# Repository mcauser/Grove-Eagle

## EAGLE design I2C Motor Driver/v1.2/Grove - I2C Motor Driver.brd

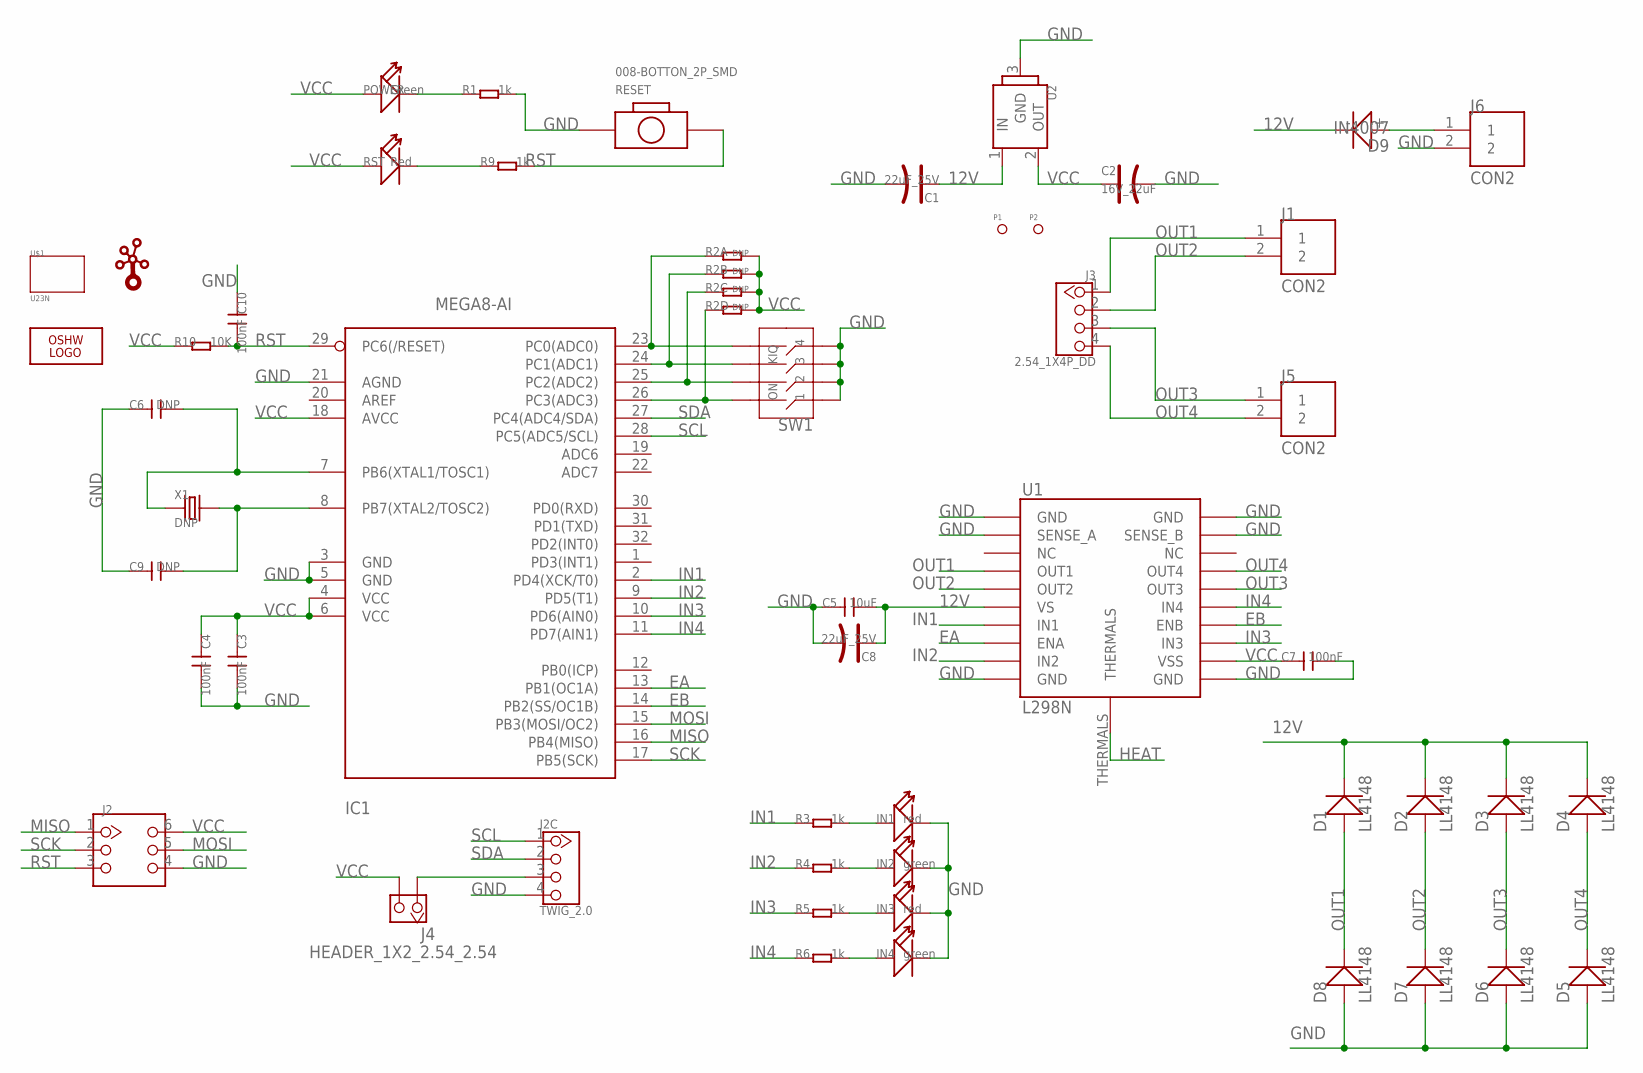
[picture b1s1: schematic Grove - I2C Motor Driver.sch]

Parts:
C1, C8: 22uF_25V; AVX-C
C2: 16V_22uF; AVX-B
C3, C4, C7: 100nF; 0603
C5: 10uF; 0805
C6, C9: DNP; 0603_S
C10: 100nF; 0603_S
D1, D2, D3, D4, D5, D6, D7, D8: LL4148; SOD123
D9: IN4007; D2010@1
I2C: TWIG_2.0; 2.0_1X4
IC1: MEGA8-AI; TQFP32-08
IN1, IN3: red; D0603
IN2, IN4: green; D0603
J1, J5, J6: CON2
J2: HEADER-2X3P-60/35MIL; 2X3P-2.54-65/35MIL
J3: 2.54_1X4P_DD; CK_1X4
J4: HEADER_1X2_2.54_2.54; 65*35
LOGO2: LOGO-OSHW-FILLX0200-NT; OSHW_FILLX200_NOTEXT
P1, P2: PAD-MARK; ROUND-MARK-1.0
POWER: Green; D0603
R1, R3, R4, R5, R6, R9: 1k; 0603-1
R2: DNP; 1206-8-3.3X2.4
R10: 10K; 0603-1
RESET: 008-BOTTON_2P_SMD; BOTTON_1
RST: Red; D0603
SW1: SWITCH-KM-04'KM-04'; 8P-SMD-11.8X6.8X3.3H
U1: L298N; POWERSO20
U2: 78M05-TO252; TO252
U$1: U23N; U2*3N
U$3: TWIGLOGOTWIGLOGO_SMALL; TWIGLOGO_SMALL
X1: DNP; 2P-SMD-5X3.2

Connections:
12V: C1.+, C5.2, C8.+, D1.-, D2.-, D3.-, D4.-, D9.-, U1.P$6 (VS), U2.1 (IN)
EA: IC1.13 (PB1(OC1A)), U1.P$8 (ENA)
EB: IC1.14 (PB2(SS/OC1B)), U1.P$14 (ENB)
GND: C1.-, C2.-, C3.2, C4.2, C5.1, C6.1, C7.2, C8.-, C9.1, C10.1, D5.+, D6.+, D7.+, D8.+, I2C.4, IC1.3 (GND), IC1.5 (GND), IC1.21 (AGND), IN1.-, IN2.-, IN3.-, IN4.-, J2.4, J6.2, R1.2, RESET.1, SW1.1, SW1.2, SW1.3, SW1.4, U1.P$1 (GND), U1.P$2 (SENSE_A), U1.P$10 (GND), U1.P$11 (GND), U1.P$19 (SENSE_B), U1.P$20 (GND), U2.3 (GND)
HEAT: U1.THERMALS
IN1: IC1.2 (PD4(XCK/T0)), R3.1, U1.P$7 (IN1)
IN2: IC1.9 (PD5(T1)), R4.1, U1.P$9 (IN2)
IN3: IC1.10 (PD6(AIN0)), R5.1, U1.P$13 (IN3)
IN4: IC1.11 (PD7(AIN1)), R6.1, U1.P$15 (IN4)
MISO: IC1.16 (PB4(MISO)), J2.1
MOSI: IC1.15 (PB3(MOSI/OC2)), J2.5
unnamed: IN3.+, R5.2
unnamed: I2C.3, J4.1
unnamed: POWER.-, R1.1
unnamed: IC1.23 (PC0(ADC0)), R2.1, SW1.5
unnamed: IC1.24 (PC1(ADC1)), R2.2 (1), SW1.6
unnamed: IC1.25 (PC2(ADC2)), R2.3 (1), SW1.7
unnamed: C6.2, IC1.7 (PB6(XTAL1/TOSC1)), X1.1
unnamed: C9.2, IC1.8 (PB7(XTAL2/TOSC2)), X1.2
unnamed: R9.1, RST.-
unnamed: IC1.26 (PC3(ADC3)), R2.4 (1), SW1.8
unnamed: D9.+, J6.1
unnamed: IN1.+, R3.2
unnamed: IN2.+, R4.2
unnamed: IN4.+, R6.2
OUT1: D1.+, D8.-, J1.1, J3.1, U1.P$4 (OUT1)
OUT2: D2.+, D7.-, J1.2, J3.2, U1.P$5 (OUT2)
OUT3: D3.+, D6.-, J3.3, J5.1, U1.P$16 (OUT3)
OUT4: D4.+, D5.-, J3.4, J5.2, U1.P$17 (OUT4)
RST: C10.2, IC1.29 (PC6(/RESET)), J2.3, R9.2, R10.2, RESET.P$2 (2)
SCK: IC1.17 (PB5(SCK)), J2.2
SCL: I2C.1, IC1.28 (PC5(ADC5/SCL))
SDA: I2C.2, IC1.27 (PC4(ADC4/SDA))
VCC: C2.+, C3.1, C4.1, C7.1, IC1.4 (VCC), IC1.6 (VCC), IC1.18 (AVCC), J2.6, J4.2, POWER.+, R2.5 (2), R2.6 (2), R2.7 (2), R2.8 (2), R10.1, RST.+, U1.P$12 (VSS), U2.2 (OUT)

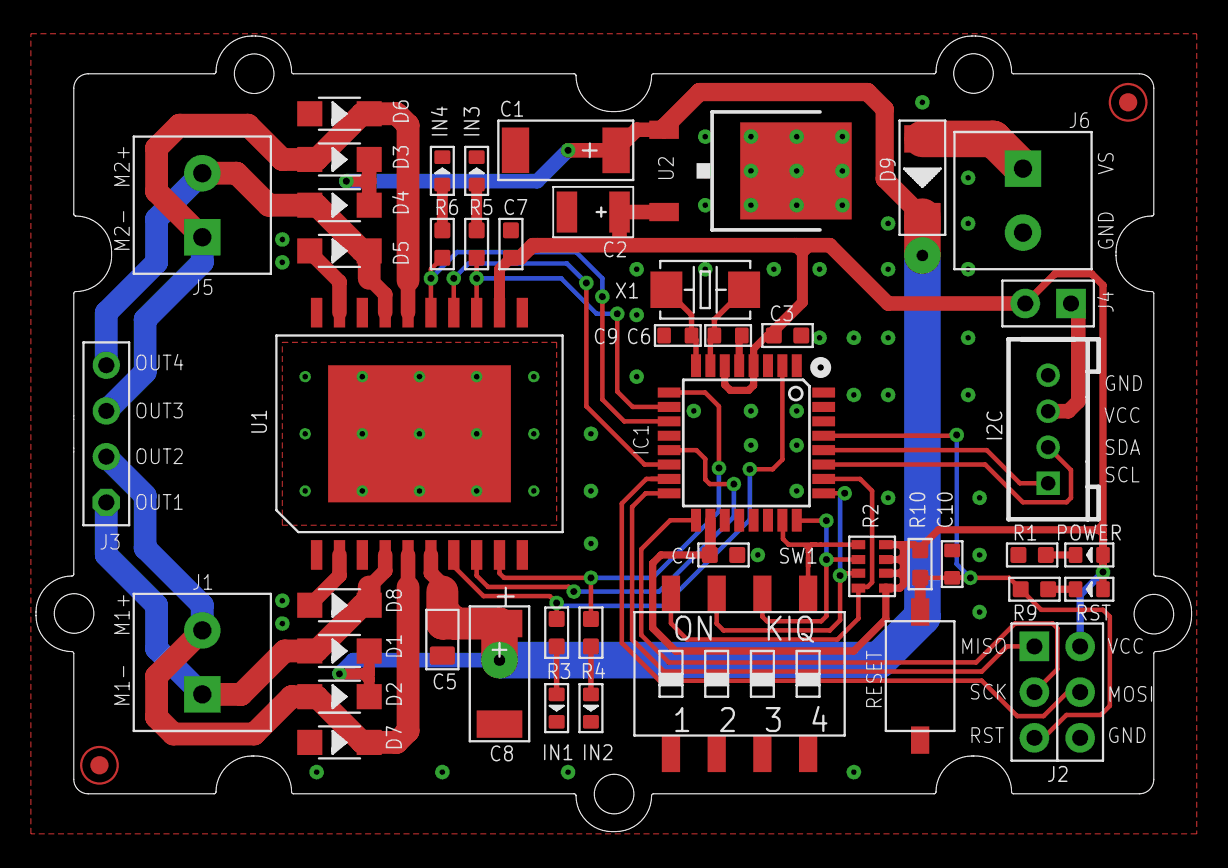
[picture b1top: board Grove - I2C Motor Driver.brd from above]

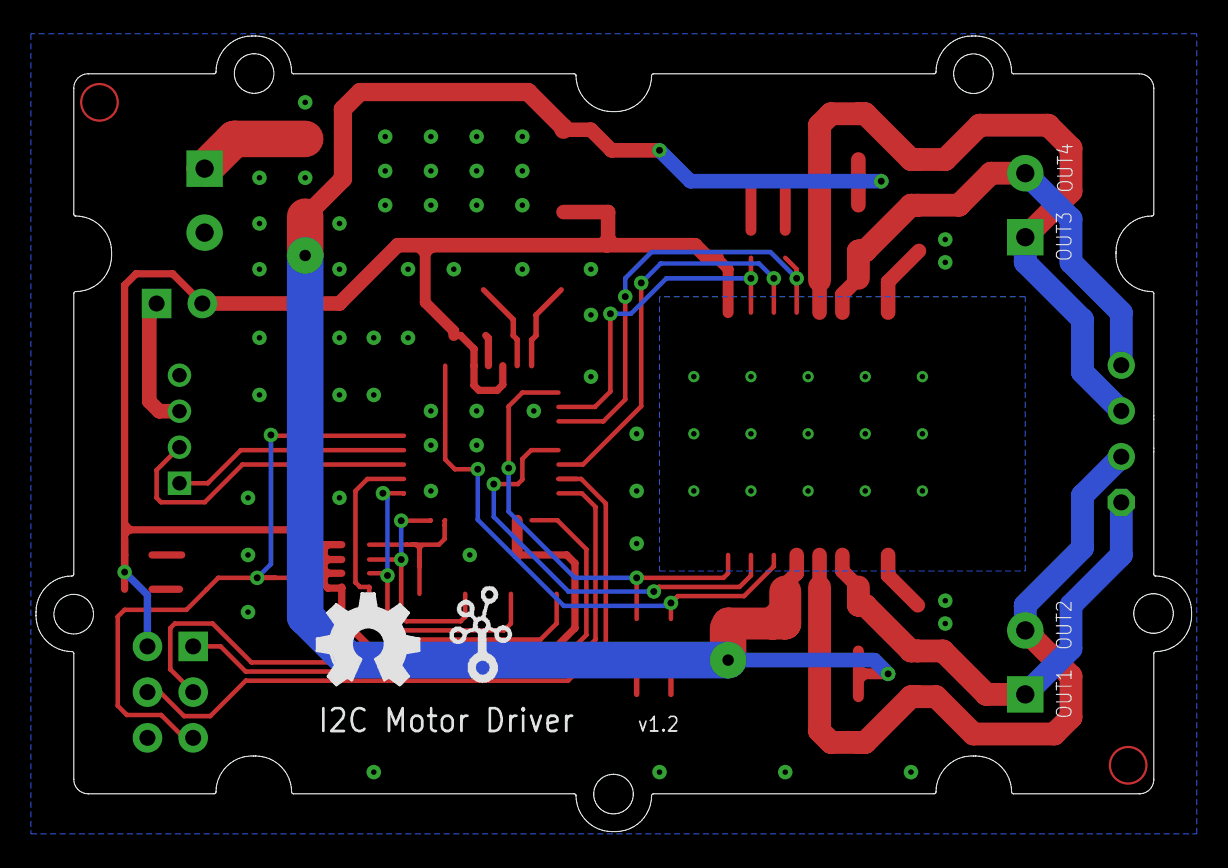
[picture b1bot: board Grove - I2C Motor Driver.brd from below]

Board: 2 copper layers, 64.2 x 44.2 mm, 51 parts (2 on the bottom side), 33 nets.

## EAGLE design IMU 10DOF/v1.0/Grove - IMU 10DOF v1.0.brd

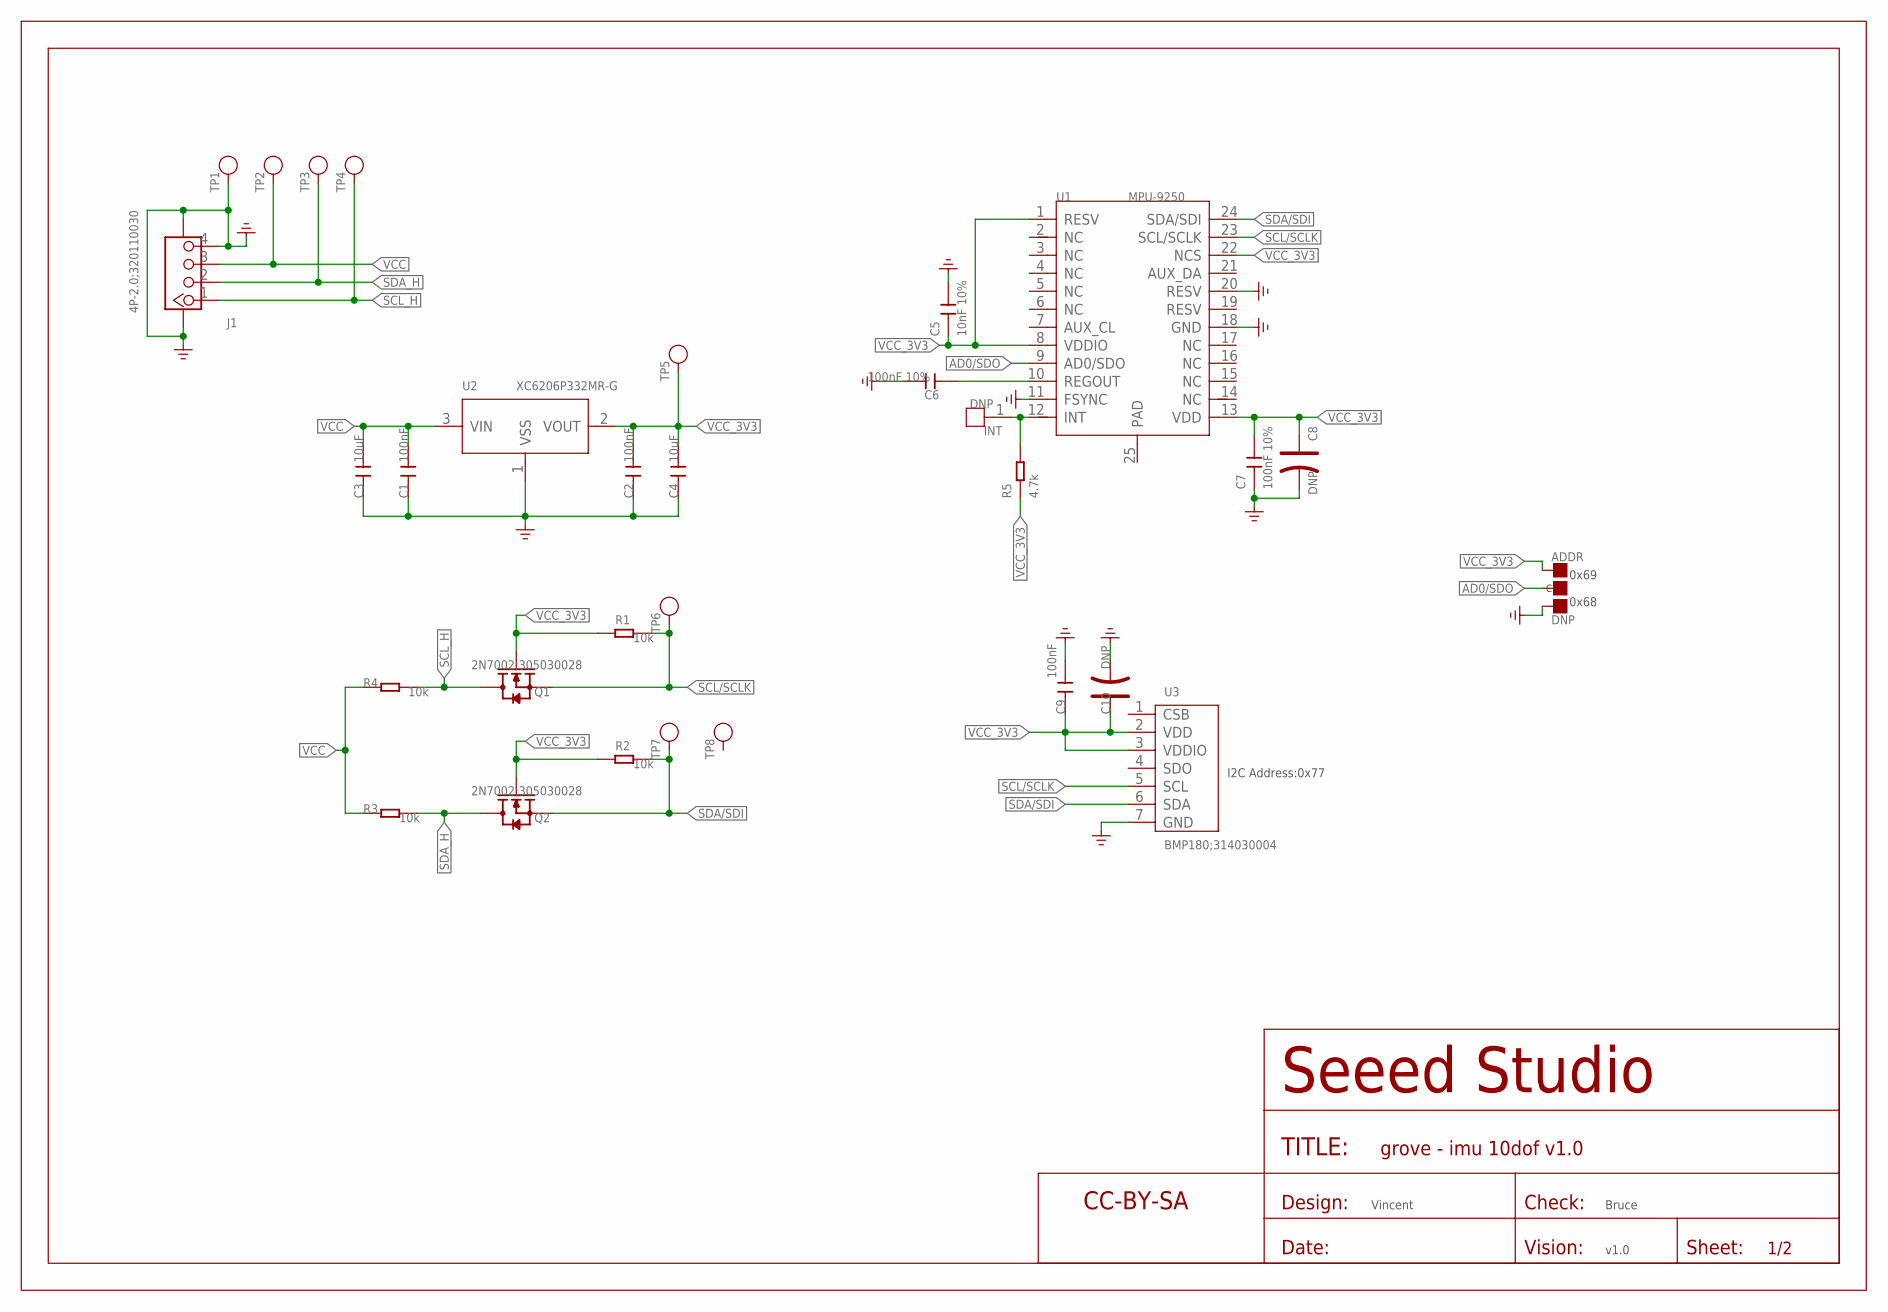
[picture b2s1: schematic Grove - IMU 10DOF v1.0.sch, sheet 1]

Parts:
ADDR: DNP; 3P-SMD-L4.1*W1.5MM
C1, C2, C9: 100nF; C0603
C3, C4: 10uF; C0805
C5: 10nF 10%; C0603
C6, C7: 100nF 10%; C0603
C8, C10: DNP; AVX-A
INT: DNP; 1P-65/35MIL
J1: 4P-2.0;320110030; 4P-SMD-2.0
Q1, Q2: 2N7002;305030028; SOT-23
R1, R2, R3, R4: 10k; R0603
R5: 4.7k; R0603
TP1, TP2, TP3, TP4, TP5, TP6, TP7, TP8: DNP; TP-D45MIL
U1: MPU-9250; LEAD-QFN24
U2: XC6206P332MR-G; SOT-23
U3: BMP180;314030004; LGA-7
U$1: SEEEDSTUDIO-OPEN-SCH-FRAME; SEEEDSTUDIO-PCB-FRAME

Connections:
AD0/SDO: ADDR.MM (C), U1.9 (AD0/SDO)
GND: ADDR.11 (R), C1.1, C2.1, C3.1, C4.1, C5.2, C6.2, C7.1, C8.-, C9.2, C10.-, J1.4, J1.SS1, J1.SS2, TP1.T, U1.11 (FSYNC), U1.18 (GND), U1.20 (RESV), U2.1 (VSS), U3.7 (GND)
unnamed: C6.1, U1.10 (REGOUT)
unnamed: INT.1, R5.2, U1.12 (INT)
SCL/SCLK: Q1.2 (S), R1.2, TP6.T, U1.23 (SCL/SCLK), U3.5 (SCL)
SCL_H: J1.1, Q1.3 (D), R4.2, TP4.T
SDA/SDI: Q2.2 (S), R2.2, TP7.T, U1.24 (SDA/SDI), U3.6 (SDA)
SDA_H: J1.2, Q2.3 (D), R3.2, TP3.T
VCC: C1.2, C3.2, J1.3, R3.1, R4.1, TP2.T, U2.3 (VIN)
VCC_3V3: ADDR.00 (L), C2.2, C4.2, C5.1, C7.2, C8.+, C9.1, C10.+, Q1.1 (G), Q2.1 (G), R1.1, R2.1, R5.1, TP5.T, U1.1 (RESV), U1.8 (VDDIO), U1.13 (VDD), U1.22 (NCS), U2.2 (VOUT), U3.2 (VDD), U3.3 (VDDIO)

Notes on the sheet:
Vincent
Bruce
v1.0
0x69
0x68
I2C Address:0x77

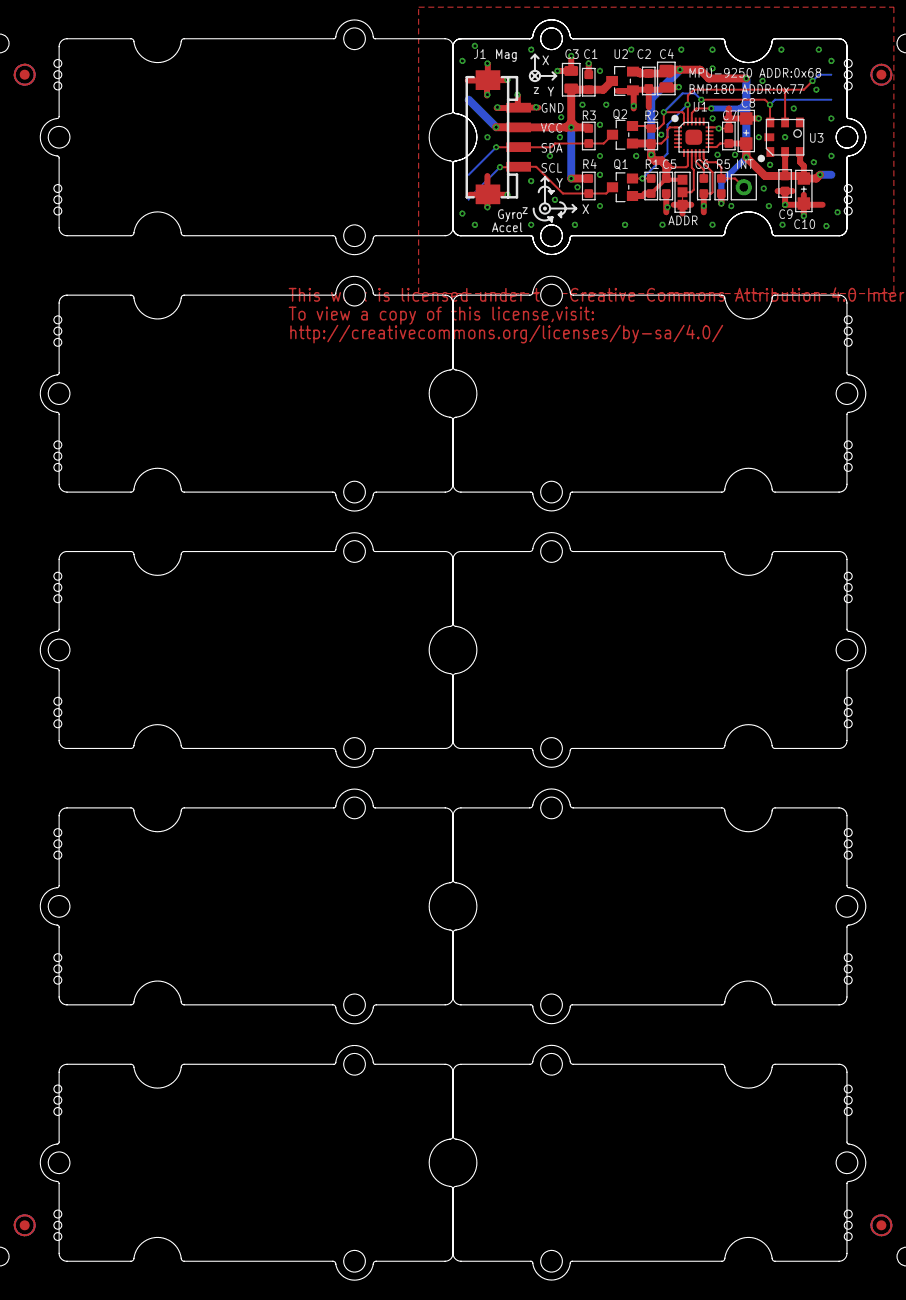
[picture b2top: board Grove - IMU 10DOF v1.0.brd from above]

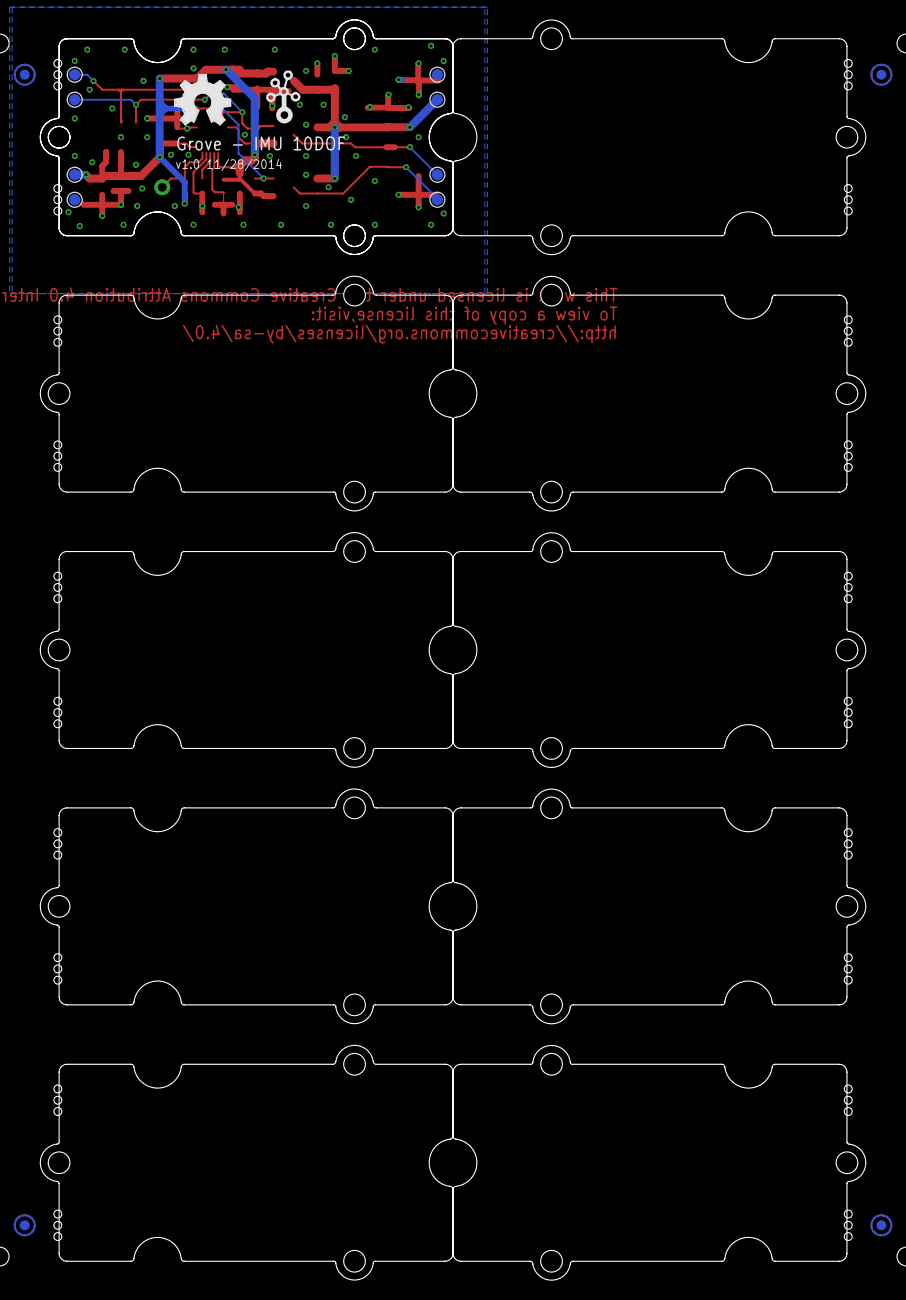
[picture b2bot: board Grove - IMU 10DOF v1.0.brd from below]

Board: 2 copper layers, 83.8 x 128.0 mm, 53 parts (14 on the bottom side), 10 nets.

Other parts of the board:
P1, P2, P3, P4, P5, P6, P7, P8: ROUND-MARK-1.0
U4, U5, U6, U7, U8, U9, U10, U11, U12, U13: GROVE-TEST-PLATFORM
U$15: GROVE-1*2-TEST-PLATFORM
U$16: GROVE-SILK-SMALL
U$17: OSHW_FILLX200_NOTEXT

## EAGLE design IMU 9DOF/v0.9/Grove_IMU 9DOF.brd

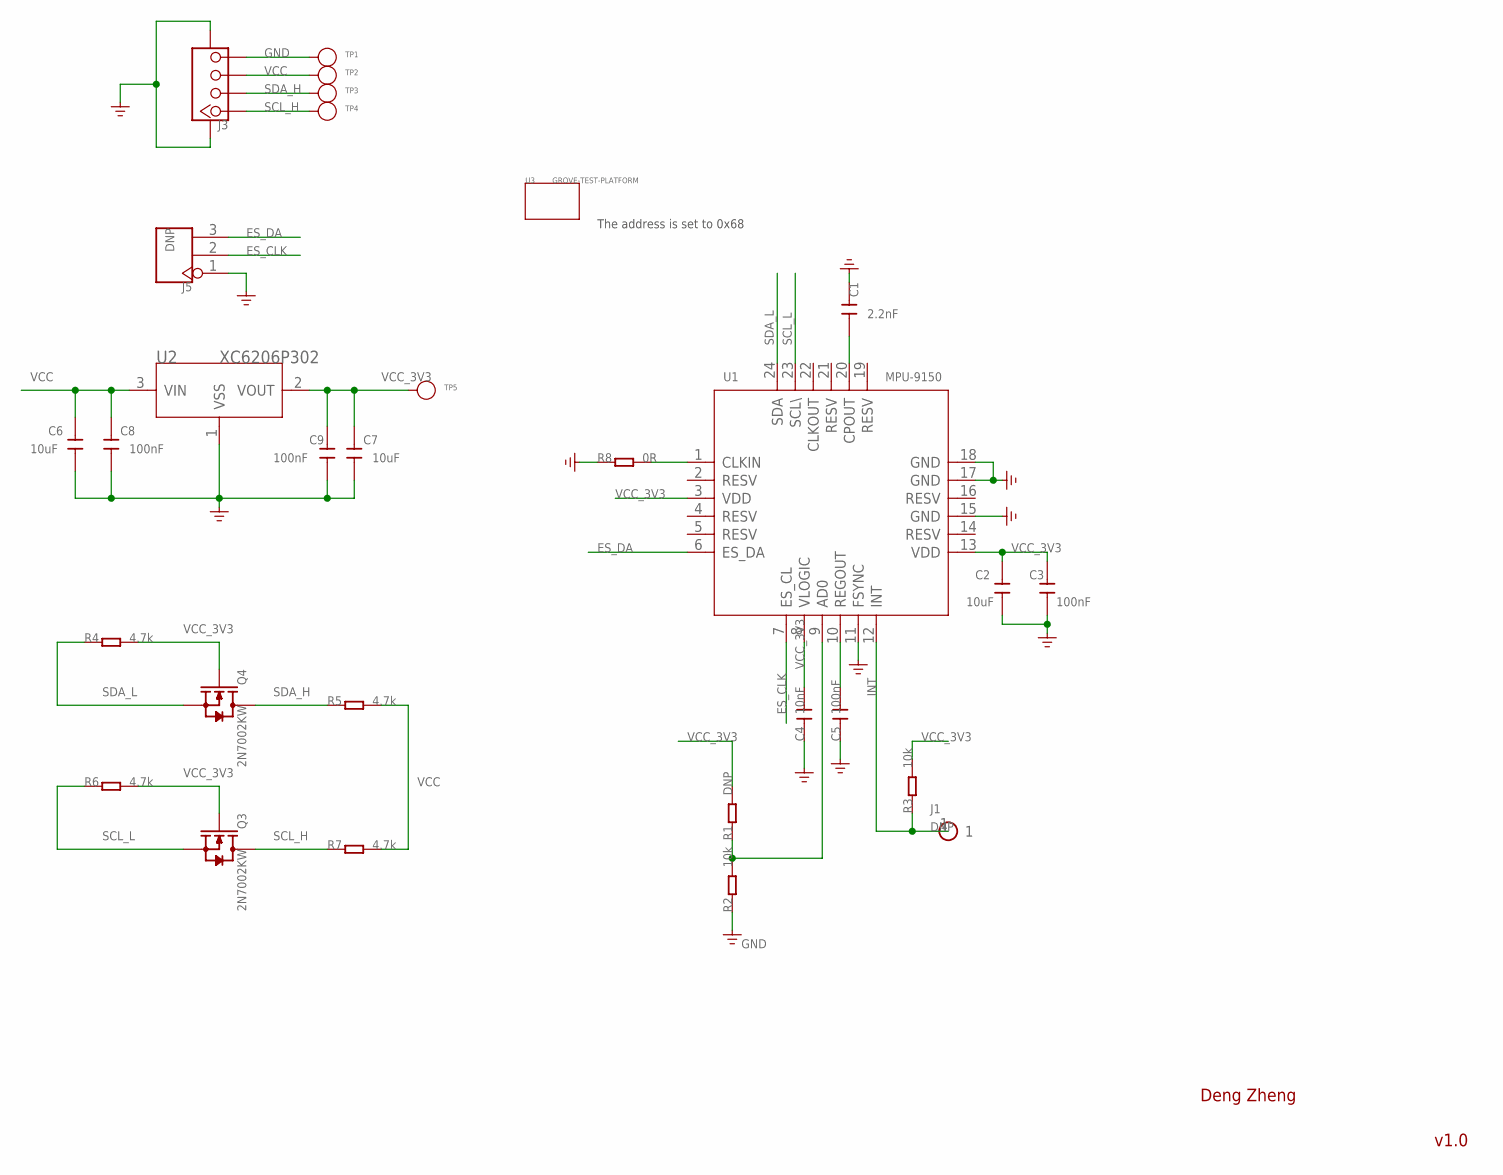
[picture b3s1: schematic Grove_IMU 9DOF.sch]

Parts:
C1: 2.2nF; C0603
C2, C6, C7: 10uF; C0805
C3, C5, C8, C9: 100nF; C0603
C4: 10nF; C0603
J1: DNP; 1P-65/35MIL
J3: TWIG-4P-2.0-SMD-FEMALE-REINFORCE'90D'; 4P-SMD-2.0-90D
J5: DNP; 3P-2.54
Q3, Q4: 2N7002KW; SOT323
R1: DNP; R0603
R2, R3: 10k; R0603
R4, R5, R6, R7: 4.7k; R0603
R8: 0R; R0603
TP1, TP2, TP3, TP4, TP5: PAD-TEST-POINT'4545'; TP_4545
U1: MPU-9150; LGA-24
U2: XC6206P302; SOT23
U3: GROVE-TEST-PLATFORM

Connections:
ES_CLK: J5.2, U1.7 (ES_CL)
ES_DA: J5.3, U1.6 (ES_DA)
GND: C1.1, C2.1, C3.1, C4.1, C5.1, C6.1, C7.1, C8.1, C9.1, J3.4, J3.SS1, J3.SS2, J5.1, R8.1, TP1.T, U1.11 (FSYNC), U1.15 (GND), U1.17 (GND), U1.18 (GND), U2.1 (VSS)
INT: J1.1, R3.1, U1.12 (INT)
unnamed: R1.1, R2.2, U1.9 (AD0)
unnamed: C1.2, U1.20 (CPOUT)
unnamed: R8.2, U1.1 (CLKIN)
unnamed: C5.2, U1.10 (REGOUT)
SCL_H: J3.1, Q3.3 (D), R7.1, TP4.T
SCL_L: Q3.2 (S), R6.1, U1.23 (SCL\)
SDA_H: J3.2, Q4.3 (D), R5.1, TP3.T
SDA_L: Q4.2 (S), R4.1, U1.24 (SDA)
VCC: C6.2, C8.2, J3.3, R5.2, R7.2, TP2.T, U2.3 (VIN)
VCC_3V3: C2.2, C3.2, C4.2, C7.2, C9.2, Q3.1 (G), Q4.1 (G), R1.2, R3.2, R4.2, R6.2, TP5.T, U1.3 (VDD), U1.8 (VLOGIC), U1.13 (VDD), U2.2 (VOUT)

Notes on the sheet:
Deng Zheng
v1.0
The address is set to 0x68

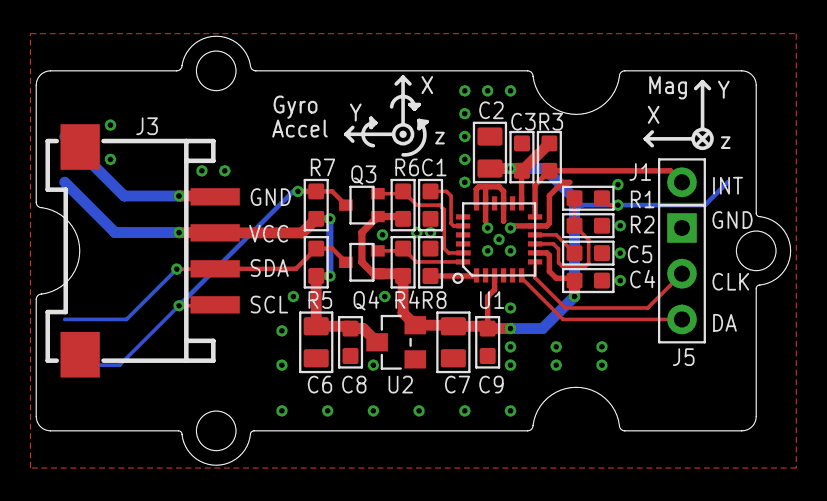
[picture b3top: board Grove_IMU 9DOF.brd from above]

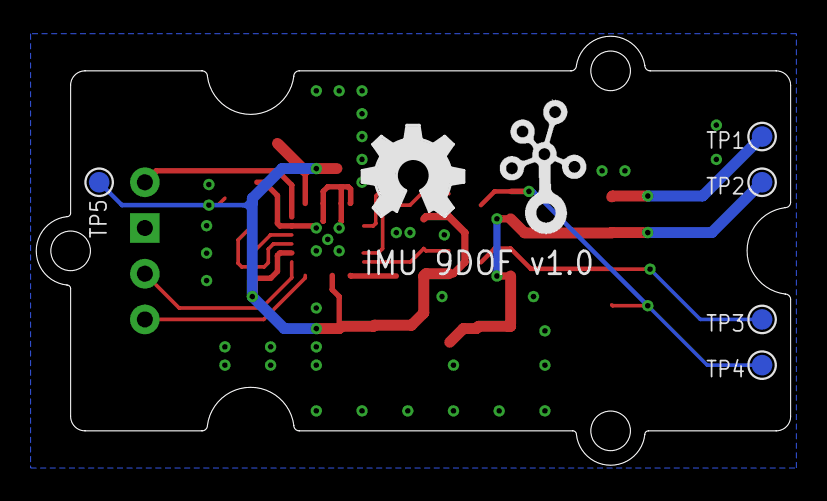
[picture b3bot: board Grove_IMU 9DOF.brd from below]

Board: 2 copper layers, 41.9 x 23.8 mm, 32 parts (7 on the bottom side), 14 nets.

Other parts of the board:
U$3: OSHW_FILLX200_NOTEXT
U$13: TWIGLOGO

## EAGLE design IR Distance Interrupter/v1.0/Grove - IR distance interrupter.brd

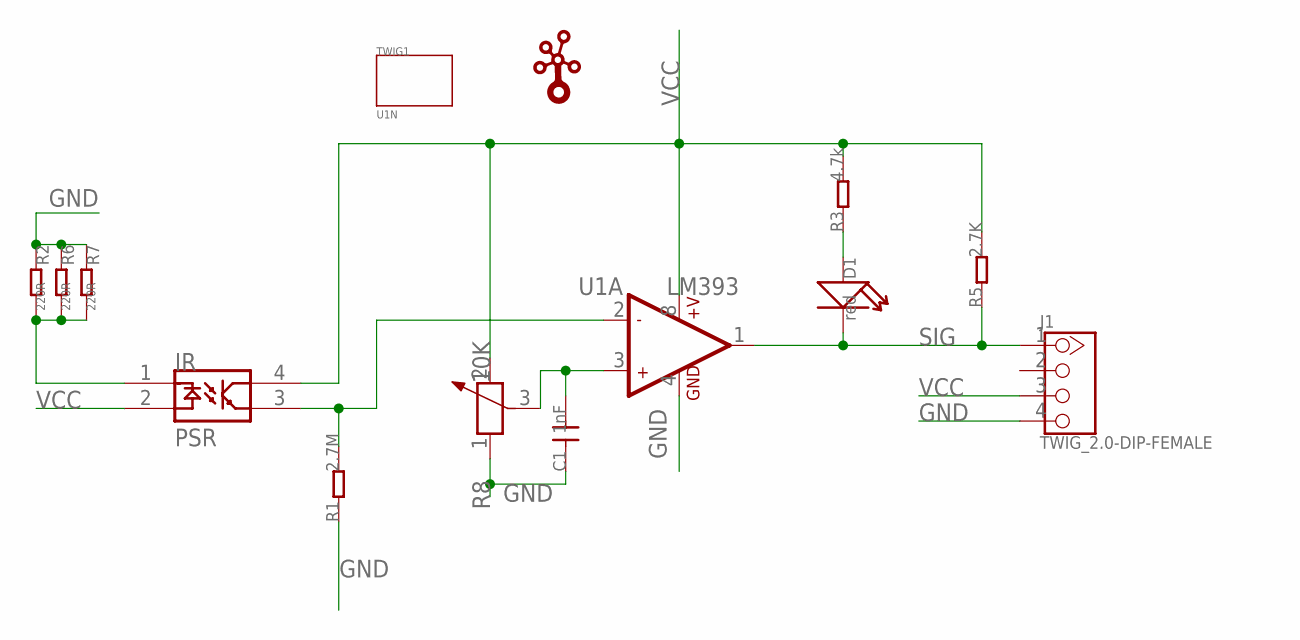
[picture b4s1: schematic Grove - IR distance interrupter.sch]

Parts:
C1: 1nF; 0603
D1: red; LED0603
J1: TWIG_2.0-DIP-FEMALE; 2.0_1X4
PSR: PSR
R1: 2.7M; 0603_S
R2, R6, R7: 220R; 0805
R3: 4.7k; 0603_S
R5: 2.7K; 0603_S
R8: 10K; 3P-SQUA-7X6.8
TWIG1: U1N
U1: LM393; SO08
U$2: TWIGLOGOTWIGLOGO_SMALL; TWIGLOGO_SMALL

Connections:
GND: C1.1, J1.4, R1.1, R2.1, R6.1, R7.1, R8.1, U1.4 (GND)
unnamed: C1.2, R8.3, U1.3 (+IN1)
unnamed: D1.1 (+), R3.1
unnamed: PSR.3, R1.2, U1.2 (-IN1)
unnamed: PSR.1, R2.2, R6.2, R7.2
SIG: D1.2 (-), J1.1, R5.1, U1.1 (OUT1)
VCC: J1.3, PSR.2, PSR.4, R3.2, R5.2, R8.2, U1.8 (+V)

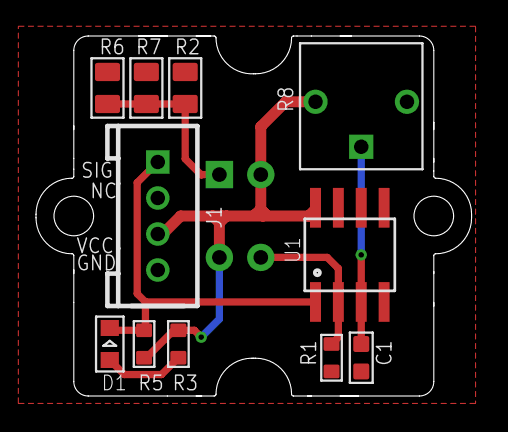
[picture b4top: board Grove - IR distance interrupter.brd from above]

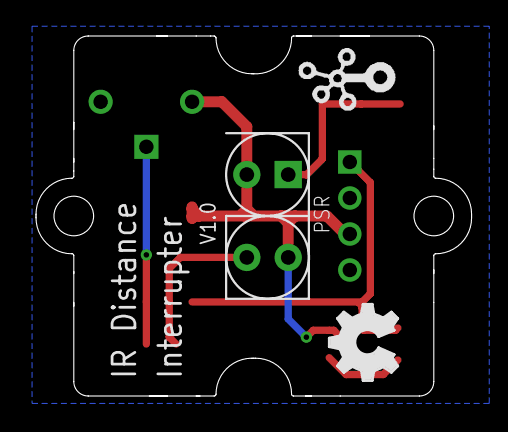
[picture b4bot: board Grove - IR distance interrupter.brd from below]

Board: 2 copper layers, 24.2 x 20.0 mm, 15 parts (3 on the bottom side), 7 nets.

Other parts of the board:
U$1: OSHW_FILLX150_NOTEXT

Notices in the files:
parts and their libraries:
moudle-new: This work is licensed under the Creative Commons Attribution 4.0 International License.
To view a copy of this license,visit:
http://creativecommons.org/licenses/by-sa/4.0
moudle-new: CC-BY-SA
